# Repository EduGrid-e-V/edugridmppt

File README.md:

<h1 align="center">EduGrid MPPT</h1>

<p align="center">
  <strong>Learn solar energy by trying it.</strong><br>
  A friendly, open-source learning kit for renewable energy education.
</p>

<p align="center">
  
  &nbsp;&nbsp;
  
</p>

EduGrid MPPT is part of the EduGrid e.V initiative for free education in renewable energies. It is made for students, teachers, workshops, and curious people who want to understand solar power with their own hands.

You do not need to be an expert to begin. Start by moving the slider, watching the display, and seeing how much power a small solar panel can produce. Later, when you feel ready, you can open the code and teach the board your own strategy for finding more power.

## What You Can Discover

- How sunlight becomes electrical power.
- Why a solar panel has a "best point" where it gives the most energy.
- How a small controller can search for that point automatically.
- How coding, electronics, and renewable energy connect in one real project.

This is not just a board and some code. It is a small learning environment: measure something real, ask why it happens, change one thing, and try again.

## Choose Your Path

| I want to... | Start here |
| --- | --- |
| learn the project step by step | [Student Workbook](docs/STUDENT_WORKBOOK.md) |
| upload the firmware to the board | [Firmware Instructions](firmware/README.md) |
| look at the circuit and PCB | [Hardware Files](hardware/README.md) |
| explore the web dashboard | [Dashboard Source](frontend/README.md) |

## ESP32 web pages

Precompiled downloads are available from [GitHub Releases](https://github.com/EduGrid-e-V/edugridmppt/releases). Each tagged release provides an Arduino Nano `.hex`, an ESP32 `firmware.bin`, a dashboard `littlefs.bin`, and a complete ZIP with checksums, bootloader and partition images, instructions, and the standalone simulation page. GitHub Actions builds the same package on every `main` push; version tags publish it as a Release. GitLab CI also packages tagged commits as pipeline artifacts.

For an ESP32 already running the OTA-capable firmware, upload `firmware.bin` and `littlefs.bin` separately at `/admin`. The bootloader and partition images require USB flashing; do not upload them through the browser. Keep a USB recovery path available, especially for the first test release.

When connected to the board's open `EduGrid_XX` WiFi network, open
`http://192.168.4.1/` for the dashboard. In the real experiment view,
select **Downloads** in the header to find recorded CSV files. The
`/downloads` page can also be opened directly.

`http://192.168.4.1/admin` is the firmware and filesystem update page.
Neither page requires a password. Anyone connected to the open EduGrid WiFi
can update the board or delete recordings; use it in a supervised setting.
See the [firmware instructions](firmware/README.md) for the update workflow.

## For Students

Begin with the workbook and the manual experiments. Your first goal is simple: find the duty setting where the solar panel produces the most power.

When you are ready to code, your workspace is:

```text
firmware/src/mppt_alg.cpp
```

Small changes are welcome. Good experiments often begin with "What happens if I try this?"

## For Teachers

EduGrid MPPT is designed for gentle entry and deeper follow-up. A first lesson can stay fully practical: connect the board, change the operating point, and discuss power. Later lessons can introduce algorithms, sensor data, dashboards, and the structure of embedded software.

The [Student Workbook](docs/STUDENT_WORKBOOK.md) is written so it can be used in class or exported as a PDF for home study.

## The Bigger Picture

EduGrid e.V works to make renewable energy education freely available. This project supports that mission with open learning material, open hardware files, and firmware that students can actually read and change.

Renewable energy becomes less mysterious when learners can touch it, measure it, and improve it. That is the spirit of EduGrid MPPT.

## License

Hardware, firmware, and documentation are each released under different open licenses. See [LICENSE.md](LICENSE.md) for details.

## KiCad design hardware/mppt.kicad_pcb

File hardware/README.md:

# EduGrid MPPT Hardware

This folder contains the KiCad hardware design files for the EduGrid MPPT trainer.

## Main Files

| File or folder | Purpose |
| --- | --- |
| `mppt.kicad_pro` | KiCad project file |
| `mppt.kicad_sch` | Schematic |
| `mppt.kicad_pcb` | PCB layout |
| `library/Library.pretty/` | Project footprints |
| `library/3dmodels/` | 3D models used by the board |
| `mppt-backups/` | KiCad backup files |

## Related Documentation

- [Student Workbook](../docs/STUDENT_WORKBOOK.md) explains the system concept and classroom experiments.
- [Firmware README](../firmware/README.md) explains the firmware, board controls, and supported build environments.

## Notes For Students

The hardware is the physical part of the MPPT system: solar panel input, buck converter power stage, INA226 sensors, OLED display, button, potentiometer, and the Arduino Nano or Arduino Nano ESP32.

When reading the schematic, try to connect each block to the firmware modules:

- Sensors in hardware are read by `firmware/src/sensor_manager.cpp`.
- The gate driver/PWM path is controlled by `firmware/src/pwm_manager.cpp`.
- Button and potentiometer are handled by `firmware/src/input_manager.cpp`.
- Display wiring is used by `firmware/src/display_manager.cpp`.

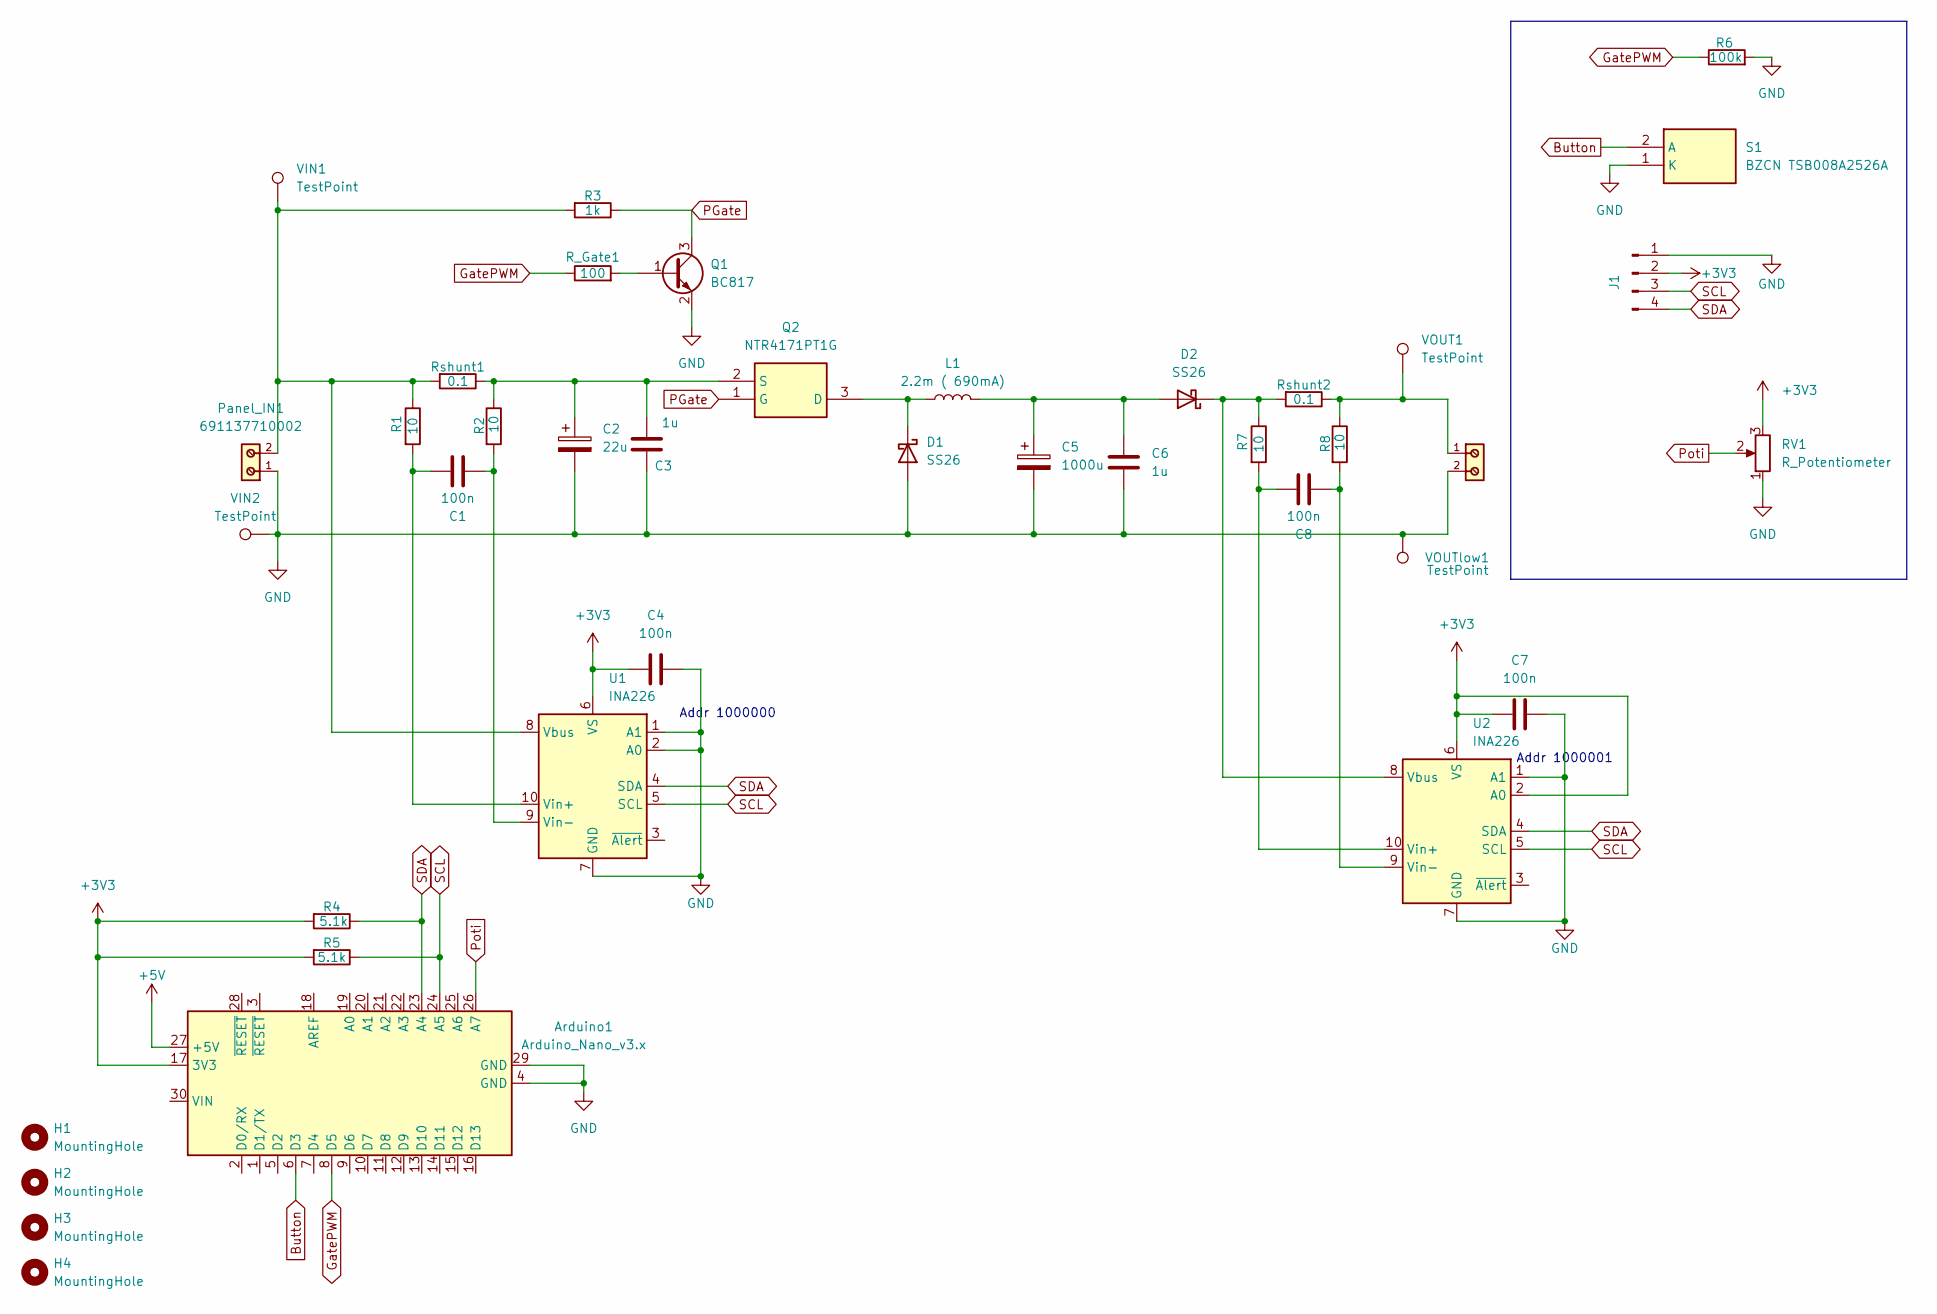
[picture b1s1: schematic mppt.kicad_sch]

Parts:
Arduino1: Arduino_Nano_v3.x; Arduino_Nano
C1, C4, C7, C8: 100n; C_0805_2012Metric_Pad1.18x1.45mm_HandSolder; LCSC Part # C49678
C2: 22u; CP_Elec_6.3x5.4; LCSC Part # C98744
C3, C6: 1u; C_0805_2012Metric_Pad1.18x1.45mm_HandSolder; LCSC Part # C28323
C5: 1000u; C_Elec_10x10.2; LCSC Part # C401766
D1, D2: SS26; D_SMA; LCSC Part # C47071
H1, H2, H3, H4: MountingHole; MountingHole_3.2mm_M3
J1: Conn_01x04_Pin; PinHeader_1x04_P2.54mm_Vertical
L1: 2.2m ( 690mA); L_Coilcraft_MSS1514V-XXX; LCSC Part # C970554
Panel_IN1: 691137710002
Q1: BC817; SOT-23; LCSC Part # C6807710
Q2: NTR4171PT1G; SOT-23; Manufacturer_Part_Number NTR4171PT1G; Mouser Part Number 863-NTR4171PT1G
R1, R2, R7, R8: 10; R_0805_2012Metric_Pad1.20x1.40mm_HandSolder; LCSC Part # C2907296
R3: 1k; R_0805_2012Metric_Pad1.20x1.40mm_HandSolder; LCSC Part # C17513
R4, R5: 5.1k; R_0805_2012Metric_Pad1.20x1.40mm_HandSolder; LCSC Part # C27834
R6: 100k; LED_0805_2012Metric_Pad1.15x1.40mm_HandSolder
RV1: R_Potentiometer; Potentiometer_Bourns_PTA4543_Single_Slide; JLCPCB Part # C17444183
R_Gate1: 100; R_0805_2012Metric_Pad1.20x1.40mm_HandSolder; LCSC Part # C17408
Rshunt1, Rshunt2: 0.1; R_2512_6332Metric_Pad1.40x3.35mm_HandSolder; LCSC Part # C1021528
S1: BZCN TSB008A2526A; SW_SPST_CK_RS282G05A3; Manufacturer_Part_Number B3U-1000P; Mouser Part Number 653-B3U-1000P
U1, U2: INA226; MSOP-10_3x3mm_P0.5mm; JLCPCB Part # C49851
VIN1, VIN2: TestPoint; TestPoint_Keystone_5005-5009_Compact; LCSC Part # C2906763
VOUT1: TestPoint; TestPoint_Keystone_5005-5009_Compact; LCSC Part # C2906763
VOUT2: 691137710002
VOUTlow1: TestPoint; TestPoint_Keystone_5005-5009_Compact; LCSC Part # C2906763

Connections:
+3V3: Arduino1.17 (3V3), C4.1, C7.1, J1.2, R4.2, R5.2, RV1.3, U1.6 (VS), U2.2 (A0), U2.6 (VS)
+5V: Arduino1.27 (+5V)
Button: Arduino1.6 (D3), S1.2 (A)
GND: Arduino1.4 (GND), Arduino1.29 (GND), C2.2, C3.2, C4.2, C5.2, C6.2, C7.2, D1.2 (A), J1.1, Panel_IN1.1, Q1.2 (E), R6.2, RV1.1, S1.1 (K), U1.1 (A1), U1.2 (A0), U1.7 (GND), U2.1 (A1), U2.7 (GND), VIN2.1, VOUT2.2, VOUTlow1.1
GatePWM: Arduino1.8 (D5), R6.1, R_Gate1.1
unnamed: D1.1 (K), L1.1, Q2.3 (D)
unnamed: C5.1, C6.1, D2.2 (A), L1.2
unnamed: D2.1 (K), R7.1, Rshunt2.2, U2.8 (Vbus)
unnamed: Q1.1 (B), R_Gate1.2
unnamed: C2.1, C3.1, Q2.2 (S), R2.1, Rshunt1.1
unnamed: R8.1, Rshunt2.1, VOUT1.1, VOUT2.1
unnamed: Panel_IN1.2, R1.1, R3.2, Rshunt1.2, U1.8 (Vbus), VIN1.1
unnamed: C1.1, R1.2, U1.10 (Vin+)
unnamed: C1.2, R2.2, U1.9 (Vin-)
unnamed: C8.1, R7.2, U2.10 (Vin+)
unnamed: C8.2, R8.2, U2.9 (Vin-)
PGate: Q1.3 (C), Q2.1 (G), R3.1
Poti: Arduino1.26 (A7), RV1.2
SCL: Arduino1.24 (A5), J1.3, R5.1, U1.5 (SCL), U2.5 (SCL)
SDA: Arduino1.23 (A4), J1.4, R4.1, U1.4 (SDA), U2.4 (SDA)

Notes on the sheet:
Addr 1000000
Addr 1000001

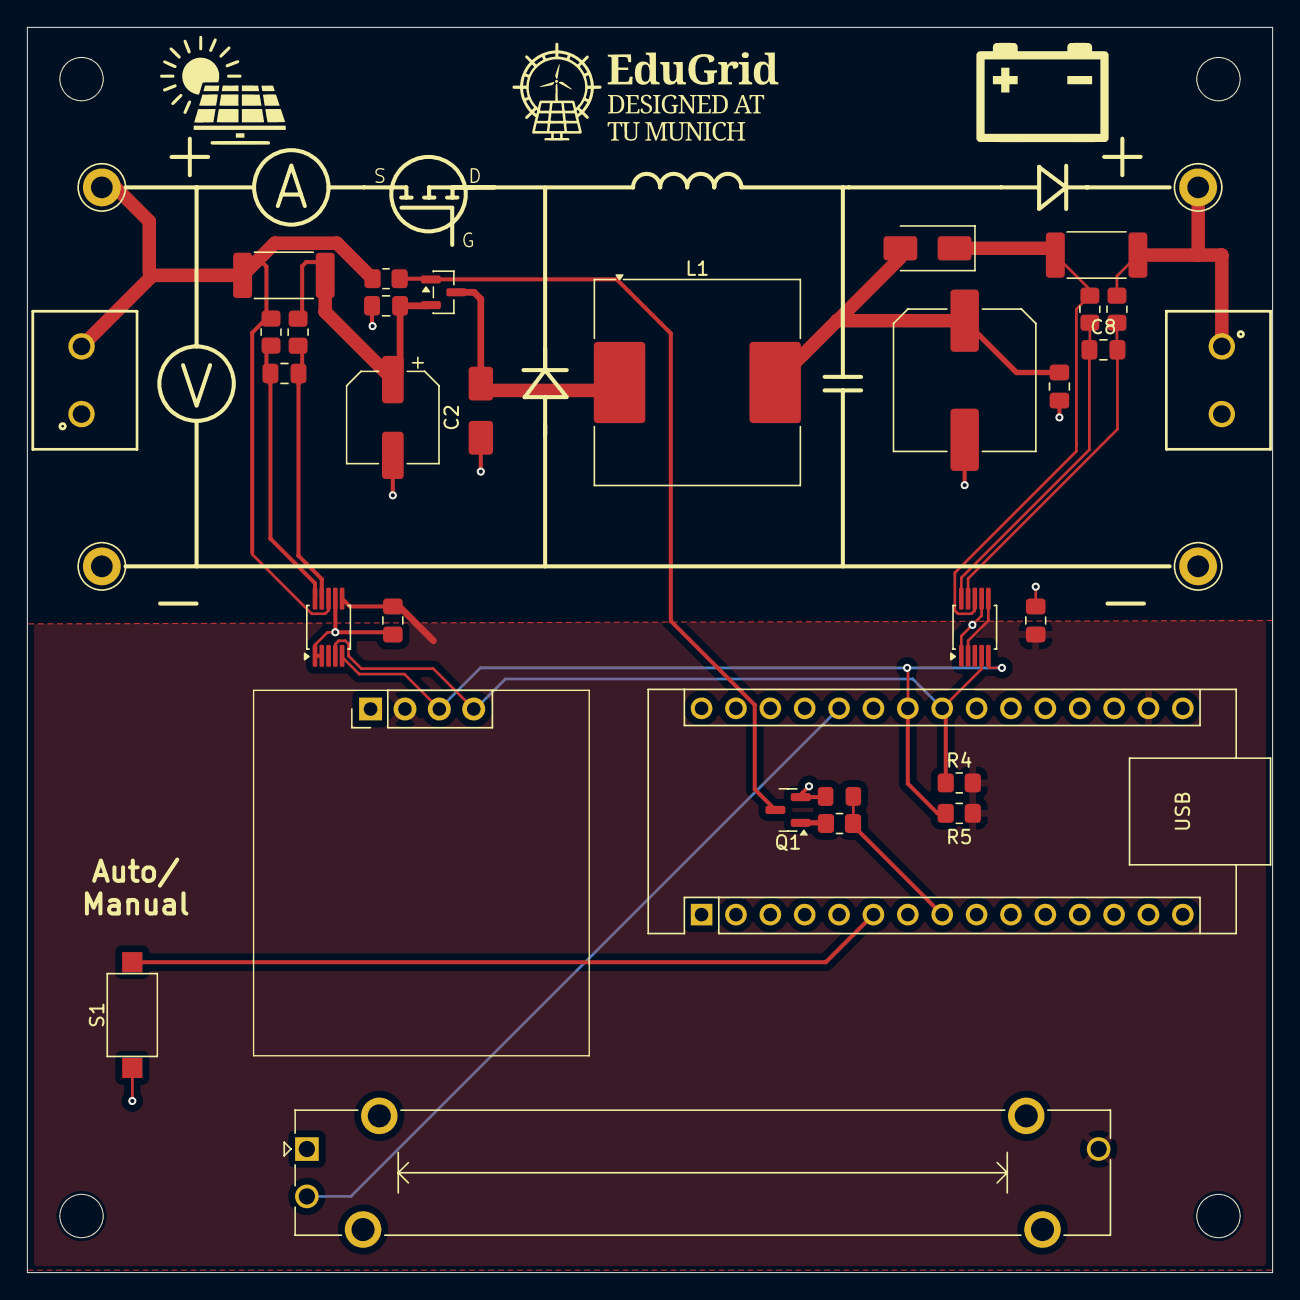
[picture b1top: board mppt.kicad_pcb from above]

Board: 2 copper layers, 92.0 x 92.0 mm, 40 parts (0 on the bottom side), 19 nets.

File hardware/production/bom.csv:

Designator,Footprint,Quantity,Value,LCSC Part #
ARDUINO1,Arduino_Nano,1,Arduino_Nano_v3.x,
"C1, C4",0805,2,100n,C49678
C2,CP_Elec_6.3x5.9,1,22u,C267472
"C3, C6",0805,2,1u,C28323
C5,C_Elec_10x10.2,1,1000u,C401766
"D1, D2",D_SMA,2,SS26,C47071
J1,PinHeader_1x04_P2.54mm_Vertical,1,Conn_01x04_Pin,
L1,L_Coilcraft_MSS1514V-XXX,1,2.2m ( 690mA),C970554
"PANEL_IN1, VOUT2",691137710002,2,691137710002,
Q1,SOT-23,1,BC817,C6807710
Q2,SOT-23,1,NTR4171PT1G,C28646357
"R1, R2",0805,2,10,C2907296
R3,0805,1,1k,C17513
"R4, R5",0805,2,5.1k,C27834
R6,0805,1,100k,
RSHUNT1,2512,1,0.1,C1021528
RV1,Potentiometer_Bourns_PTA4543_Single_Slide,1,R_Potentiometer,
R_GATE1,0805,1,100,C17408
S1,SW_SPST_CK_RS282G05A3,1,BZCN TSB008A2526A,C2888456
U1,MSOP-10_3x3mm_P0.5mm,1,INA226,C49851
"VIN1, VIN2, VOUT1, VOUTLOW1",TestPoint_Keystone_5005-5009_Compact,4,TestPoint,C2906763

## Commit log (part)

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2025-12-21 Initial commit - EduGrid MPPT with ESP32 support
2025-12-21 added readme
2025-12-21 added arduino mppt board picture
2025-12-24 added KiCad files
2025-12-24 restructured directories
2026-02-18 updated version
2026-02-18 include temporary kicad outputs
2026-02-21 added KiCad output files
2026-02-27 added measurment to output
2026-02-27 added lock file
2026-03-08 add production files
2026-03-08 update picture
2026-03-08 added output measurements and adjusted components
2026-03-08 Remove production files from tracking and respect .gitignore
2026-05-14 Complete rework of functions and frontend
2026-05-14 Connected 3.3V instead of 5V to slider poti. This makes the full range available for esp32 and avoids damage to the board
2026-05-15 minor graph adjustments
2026-06-15 added esp32c3 super mini as replacement for esp32 nano
2026-06-15 Change the WiFi SSID to include the chipID for identification when there's multiple devices. SSID is hown for 15 seconds on startup of the esp
2026-06-15 changed duty cycle limits to 0% and 98% to get a better V-I curve plot
2026-06-15 changed the power graph axis dynamically, add more precision to the measurments display
2026-06-15 changes in the frontend and added the esp32c3mini library to the kicad project
